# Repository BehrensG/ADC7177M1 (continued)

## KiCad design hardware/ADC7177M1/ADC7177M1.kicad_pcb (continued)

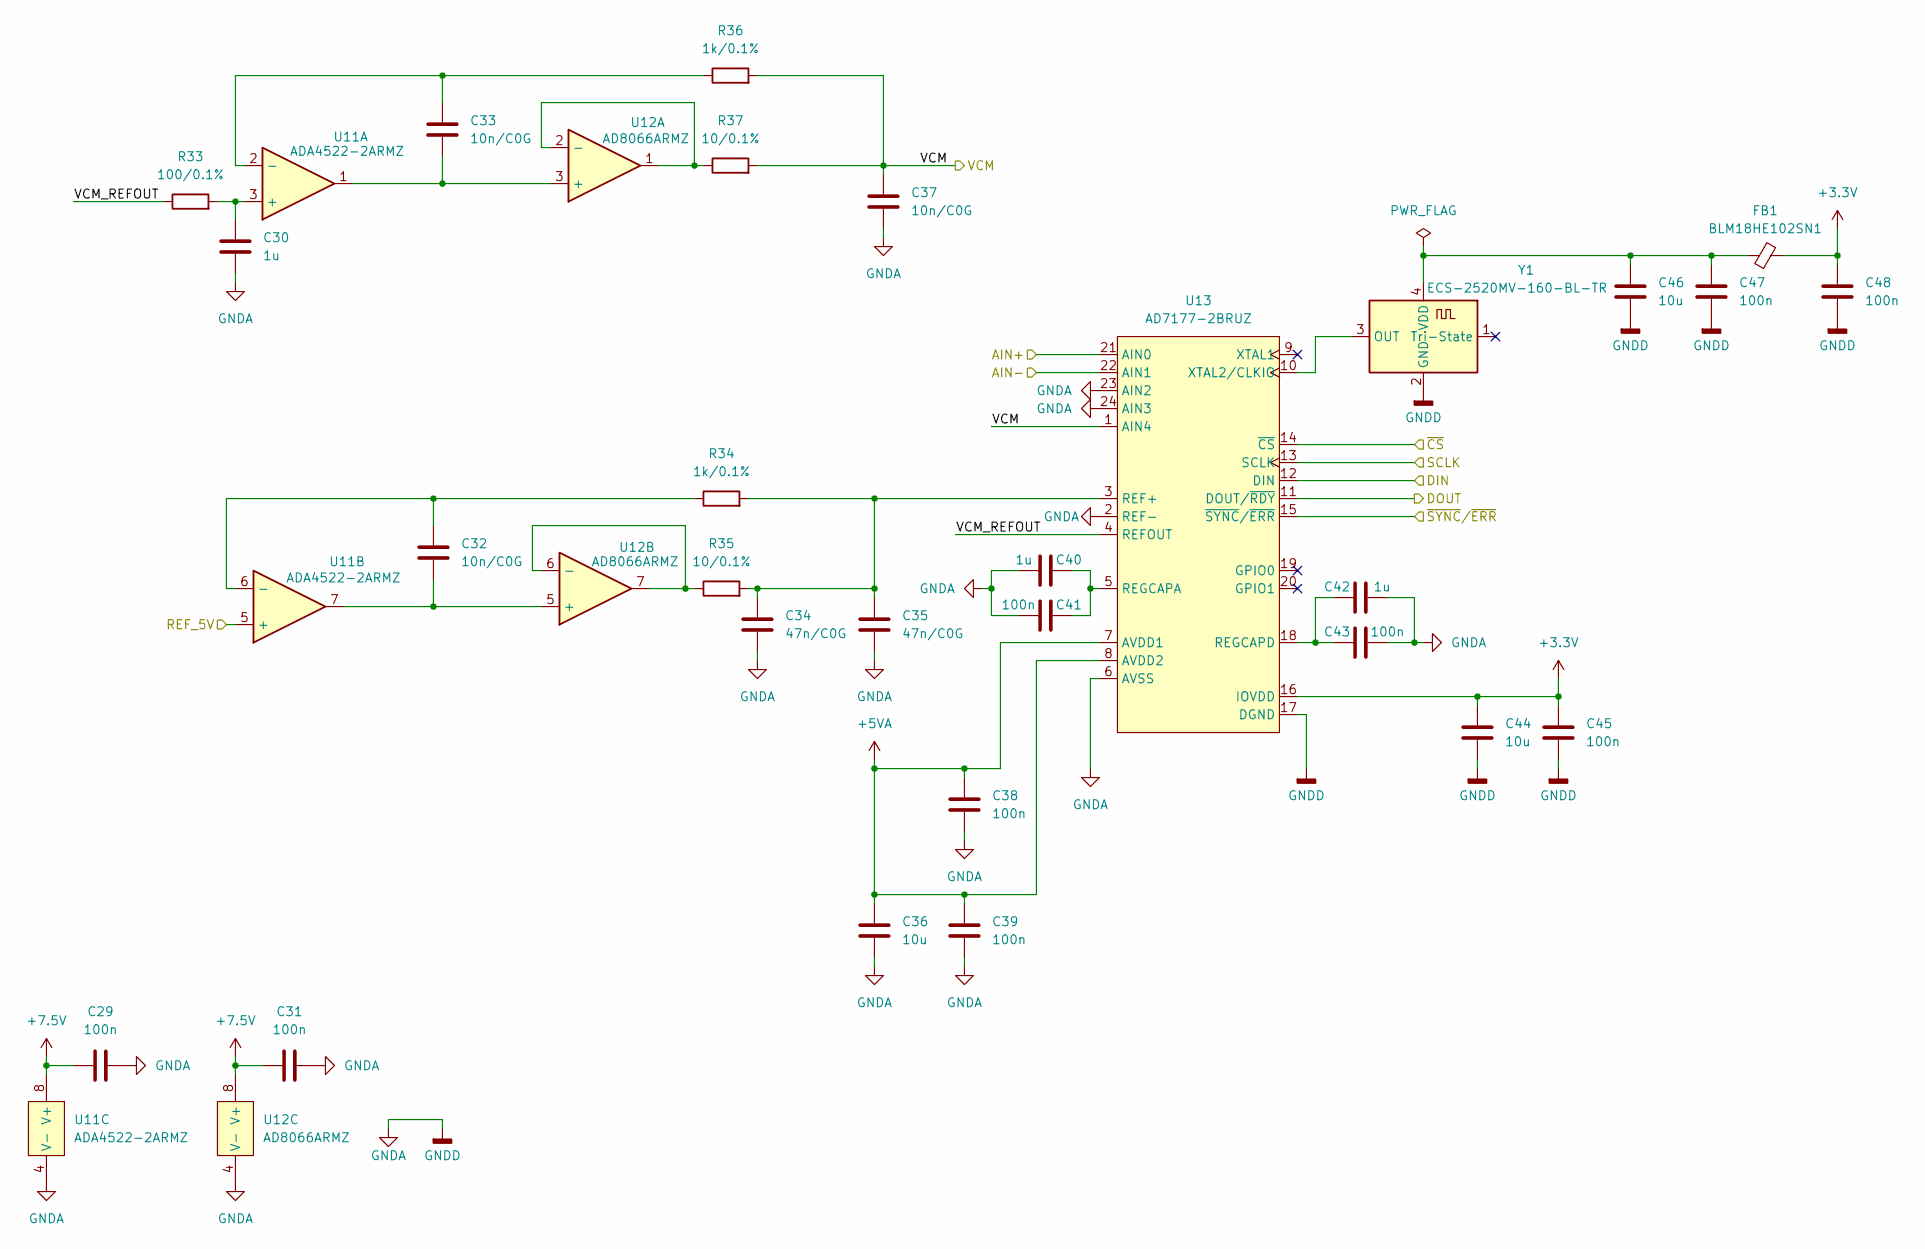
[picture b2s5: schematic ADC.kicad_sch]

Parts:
C29, C31, C38, C39, C41, C43, C45, C47, C48: 100n; C_0603_1608Metric
C30, C40, C42: 1u; C_0603_1608Metric
C32, C33, C37: 10n/C0G; C_0603_1608Metric
C34, C35: 47n/C0G; C_0603_1608Metric
C36, C44, C46: 10u; C_0805_2012Metric
FB1: BLM18HE102SN1; L_0603_1608Metric
R33: 100/0.1%; R_0603_1608Metric
R34, R36: 1k/0.1%; R_0603_1608Metric
R35, R37: 10/0.1%; R_0603_1608Metric
U11: ADA4522-2ARMZ; MSOP-8_3x3mm_P0.65mm
U12: AD8066ARMZ; MSOP-8_3x3mm_P0.65mm
U13: AD7177-2BRUZ; TSSOP-24_4.4x7.8mm_P0.65mm
Y1: ECS-2520MV-160-BL-TR; Oscillator_SMD_ECS_2520MV-xxx-xx-4Pin_2.5x2.0mm

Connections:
+3.3V: C44.1, C45.1, C48.1, FB1.2, U13.16 (IOVDD); also elsewhere on the board
+5VA: C36.1, C38.1, C39.1, U13.7 (AVDD1), U13.8 (AVDD2); also elsewhere on the board
+7.5V: C29.1, C31.1, U11.8 (V+), U12.8 (V+); also elsewhere on the board
/Schematic/ADC/AIN+: U13.21 (AIN0); also elsewhere on the board
/Schematic/ADC/AIN-: U13.22 (AIN1); also elsewhere on the board
/Schematic/ADC/DIN: U13.12 (DIN); also elsewhere on the board
/Schematic/ADC/DOUT: U13.11 (DOUT/~RDY); also elsewhere on the board
/Schematic/ADC/SCLK: U13.13 (SCLK); also elsewhere on the board
/Schematic/ADC/VCM: C37.1, R36.2, R37.2, U13.1 (AIN4); also elsewhere on the board
/Schematic/ADC/VCM_REFOUT: R33.1, U13.4 (REFOUT)
/Schematic/ADC/~CS: U13.14 (~CS); also elsewhere on the board
/Schematic/ADC/~SYNC/~ERR: U13.15 (~SYNC/~ERR); also elsewhere on the board
/Schematic/REF_5V: U11.5 (+); also elsewhere on the board
GNDA: C29.2, C30.2, C31.2, C34.2, C35.2, C36.2, C37.2, C38.2, C39.2, C40.2, C41.2, C42.2, C43.2, C44.2, C45.2, C46.2, C47.2, C48.2, U11.4 (V-), U12.4 (V-), U13.2 (REF-), U13.6 (AVSS), U13.17 (DGND), U13.23 (AIN2), U13.24 (AIN3), Y1.2 (GND); also elsewhere on the board
unnamed: C30.1, R33.2, U11.3 (+)
unnamed: C33.1, R36.1, U11.2 (-)
unnamed: C32.1, R34.1, U11.6 (-)
unnamed: C33.2, U11.1, U12.3 (+)
unnamed: R37.1, U12.1, U12.2 (-)
unnamed: C32.2, U11.7, U12.5 (+)
unnamed: R35.1, U12.6 (-), U12.7
unnamed: C34.1, C35.1, R34.2, R35.2, U13.3 (REF+)
unnamed: C40.1, C41.1, U13.5 (REGCAPA)
unnamed: C42.1, C43.1, U13.18 (REGCAPD)
unnamed: U13.10 (XTAL2/CLKIO), Y1.3 (OUT)
unnamed: C46.1, C47.1, FB1.1, Y1.4 (VDD)

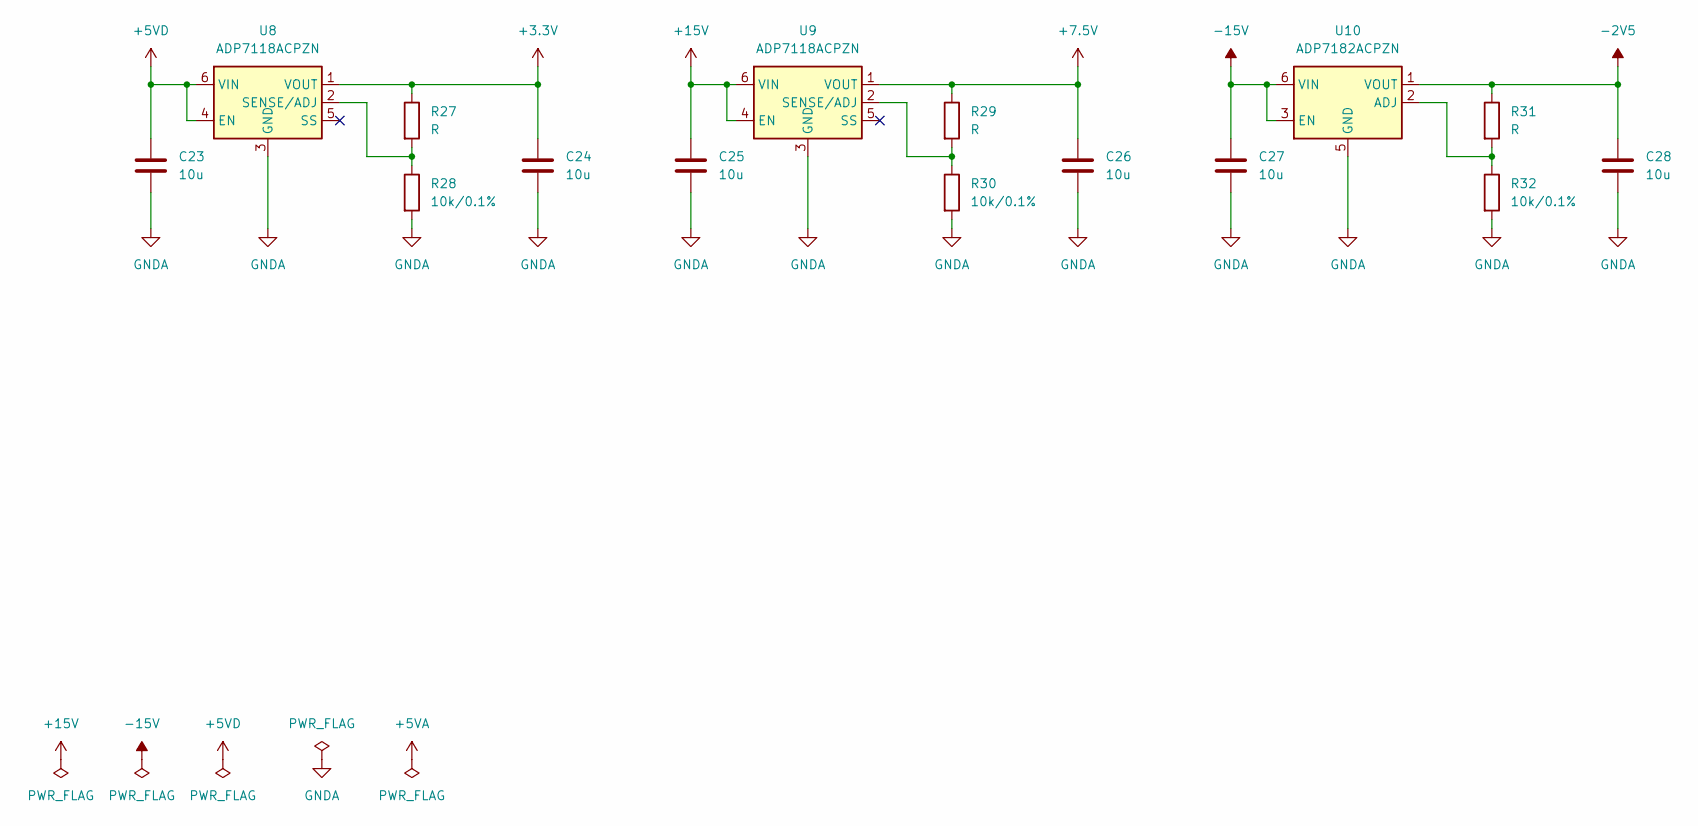
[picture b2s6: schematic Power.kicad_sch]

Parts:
C23, C24, C25, C26, C27, C28: 10u; C_0805_2012Metric
R27, R29, R31: R; R_0603_1608Metric
R28, R30, R32: 10k/0.1%; R_0603_1608Metric
U8, U9: ADP7118ACPZN; LFCSP-6-1EP_2x2mm_P0.65mm_EP1x1.6mm
U10: ADP7182ACPZN; LFCSP-6-1EP_2x2mm_P0.65mm_EP1x1.6mm

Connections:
+3.3V: C24.1, R27.1, U8.1 (VOUT); also elsewhere on the board
+5VD: C23.1, U8.4 (EN), U8.6 (VIN); also elsewhere on the board
+7.5V: C26.1, R29.1, U9.1 (VOUT); also elsewhere on the board
+15V: C25.1, U9.4 (EN), U9.6 (VIN); also elsewhere on the board
-2V5: C28.1, R31.1, U10.1 (VOUT); also elsewhere on the board
-15V: C27.1, U10.3 (EN), U10.6 (VIN), U10.7 (EP); also elsewhere on the board
GNDA: C23.2, C24.2, C25.2, C26.2, C27.2, C28.2, R28.2, R30.2, R32.2, U8.3 (GND), U8.7 (GND), U9.3 (GND), U9.7 (GND), U10.5 (GND); also elsewhere on the board
unnamed: R27.2, R28.1, U8.2 (SENSE/ADJ)
unnamed: R29.2, R30.1, U9.2 (SENSE/ADJ)
unnamed: R31.2, R32.1, U10.2 (ADJ)

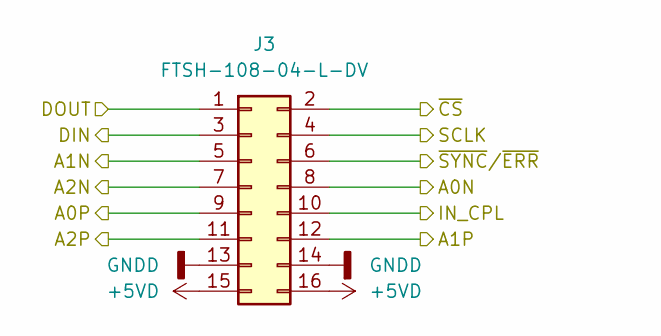
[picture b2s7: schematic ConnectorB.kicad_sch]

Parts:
J3: FTSH-108-04-L-DV; PinHeader_2x08_P1.27mm_Vertical_SMD

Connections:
+5VD: J3.15, J3.16; also elsewhere on the board
/Schematic/ADC/DIN: J3.3; also elsewhere on the board
/Schematic/ADC/DOUT: J3.1; also elsewhere on the board
/Schematic/ADC/SCLK: J3.4; also elsewhere on the board
/Schematic/ADC/~CS: J3.2; also elsewhere on the board
/Schematic/ADC/~SYNC/~ERR: J3.6; also elsewhere on the board
/Schematic/Connector B/A0N: J3.8; also elsewhere on the board
/Schematic/Connector B/A0P: J3.9; also elsewhere on the board
/Schematic/Connector B/A1N: J3.5; also elsewhere on the board
/Schematic/Connector B/A1P: J3.12; also elsewhere on the board
/Schematic/Connector B/A2N: J3.7; also elsewhere on the board
/Schematic/Connector B/A2P: J3.11; also elsewhere on the board
/Schematic/Frontend/IN_CPL: J3.10; also elsewhere on the board
GNDA: J3.13, J3.14; also elsewhere on the board

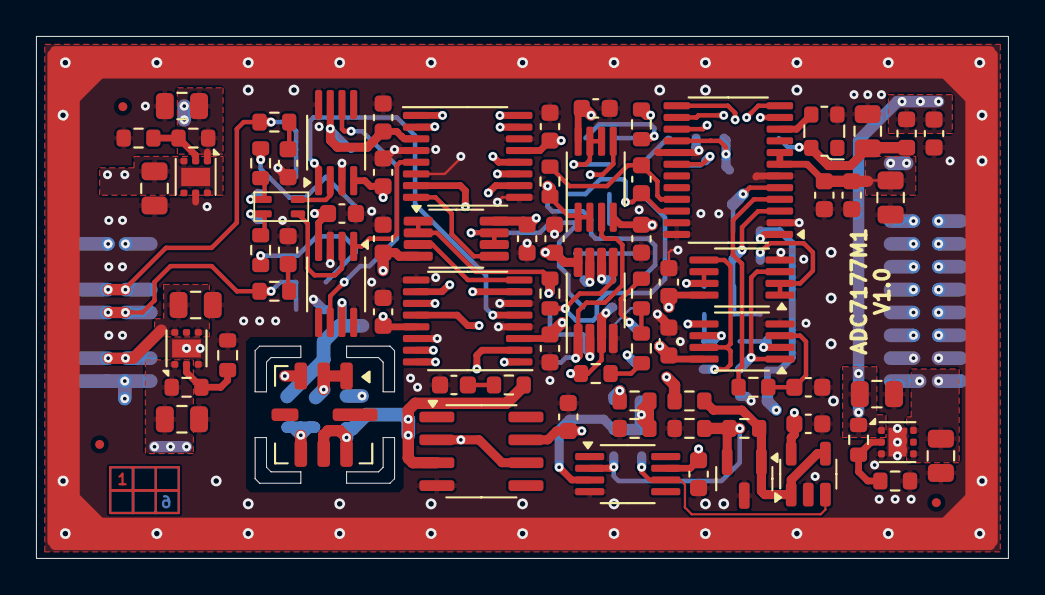
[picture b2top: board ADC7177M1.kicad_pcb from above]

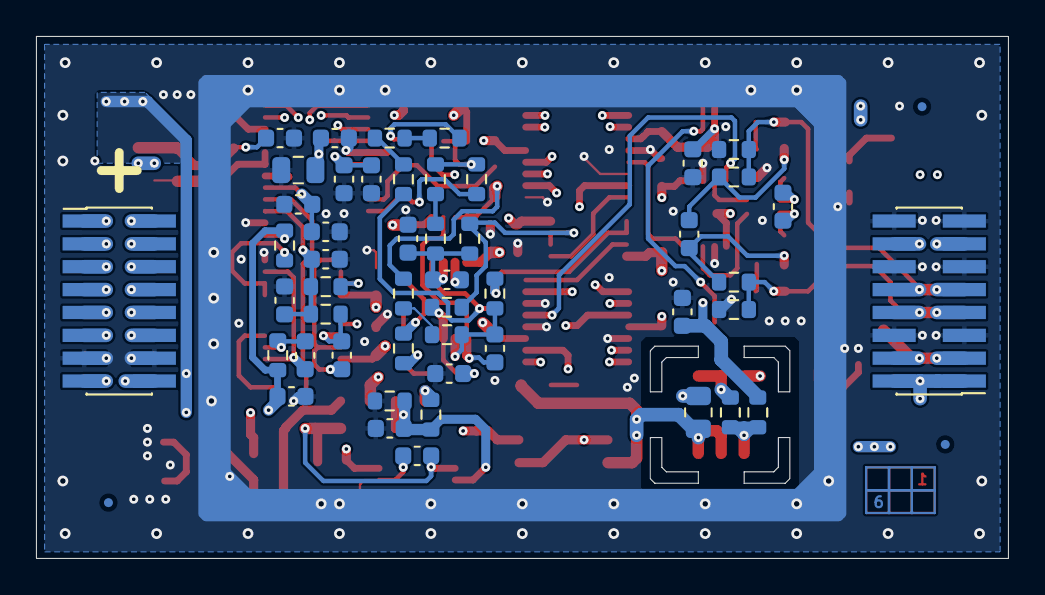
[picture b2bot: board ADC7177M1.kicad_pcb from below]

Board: 6 copper layers, 54.0 x 29.0 mm, 133 parts (53 on the bottom side), 80 nets.

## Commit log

2025-05-18 Schematic
2025-05-22 Schematic and PCB
2025-05-25 PCB and schematic
2025-05-31 Rules
2025-07-12 Schematic changes
